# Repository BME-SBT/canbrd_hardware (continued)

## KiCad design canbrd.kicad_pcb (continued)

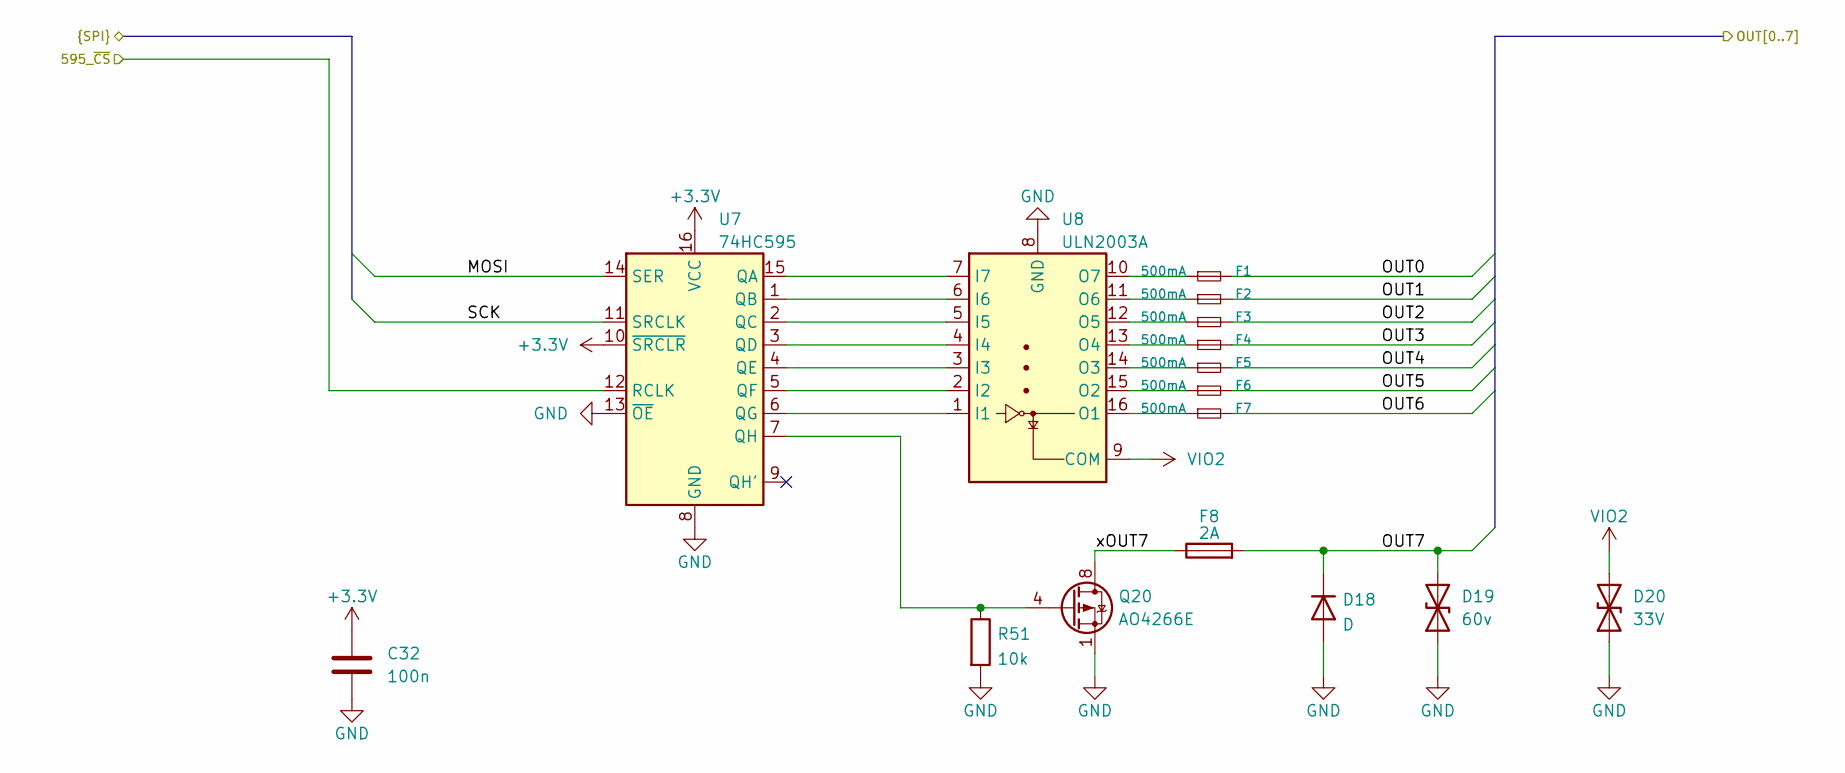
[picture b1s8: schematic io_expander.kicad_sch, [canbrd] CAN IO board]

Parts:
C32: 100n; C_0603_1608Metric
D18: D; D_SMB
D19: 60v; D_SMB
D20: 33V; D_SMB
F1, F2, F3, F4, F5, F6, F7: 500mA; Fuse_1206_3216Metric
F8: 2A; Littelfuse-154-2920
Q20: AO4266E; SOIC-8_3.9x4.9mm_P1.27mm
R51: 10k; R_0603_1608Metric
U7: 74HC595; SOIC-16_3.9x9.9mm_P1.27mm
U8: ULN2003A; SOIC-16_3.9x9.9mm_P1.27mm

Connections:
+3V3: C32.1, U7.10 (~SRCLR), U7.16 (VCC); also elsewhere on the board
/CAN/MOSI: U7.14 (SER); also elsewhere on the board
/CAN/SCK: U7.11 (SRCLK); also elsewhere on the board
/Connectors/OUT0: F1.2; also elsewhere on the board
/Connectors/OUT1: F2.2; also elsewhere on the board
/Connectors/OUT2: F3.2; also elsewhere on the board
/Connectors/OUT3: F4.2; also elsewhere on the board
/Connectors/OUT4: F5.2; also elsewhere on the board
/Connectors/OUT5: F6.2; also elsewhere on the board
/Connectors/OUT6: F7.2; also elsewhere on the board
/Connectors/OUT7: D18.1 (K), D19.2 (A2), F8.2; also elsewhere on the board
/IO Expander/595_~CS: U7.12 (RCLK); also elsewhere on the board
/IO Expander/xOUT7: F8.1, Q20.5 (D), Q20.6 (D), Q20.7 (D), Q20.8 (D)
GND: C32.2, D18.2 (A), D19.1 (A1), D20.1 (A1), Q20.1 (S), Q20.2 (S), Q20.3 (S), R51.2, U7.8 (GND), U7.13 (~OE), U8.8 (GND); also elsewhere on the board
unnamed: F1.1, U8.10 (O7)
unnamed: F2.1, U8.11 (O6)
unnamed: F3.1, U8.12 (O5)
unnamed: F4.1, U8.13 (O4)
unnamed: F5.1, U8.14 (O3)
unnamed: F6.1, U8.15 (O2)
unnamed: F7.1, U8.16 (O1)
unnamed: Q20.4 (G), R51.1, U7.7 (QH)
unnamed: U7.1 (QB), U8.6 (I6)
unnamed: U7.2 (QC), U8.5 (I5)
unnamed: U7.3 (QD), U8.4 (I4)
unnamed: U7.4 (QE), U8.3 (I3)
unnamed: U7.5 (QF), U8.2 (I2)
unnamed: U7.6 (QG), U8.1 (I1)
unnamed: U7.15 (QA), U8.7 (I7)
VIO2: D20.2 (A2), U8.9 (COM); also elsewhere on the board

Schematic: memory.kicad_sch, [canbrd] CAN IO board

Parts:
J2: Micro_SD_Card; GTFH081x1YHR
R52: 100; R_0603_1608Metric

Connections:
+3V3: J2.4 (VDD); also elsewhere on the board
/CAN/MISO: R52.1; also elsewhere on the board
/CAN/MOSI: J2.3 (CMD); also elsewhere on the board
/CAN/SCK: J2.5 (CLK); also elsewhere on the board
/MCU/SD_~CS: J2.2 (DAT3/CD); also elsewhere on the board
/SD/xMISO: J2.7 (DAT0), R52.2
GND: J2.6 (VSS), J2.9 (SHIELD); also elsewhere on the board

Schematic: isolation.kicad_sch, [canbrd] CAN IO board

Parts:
C25, C26: 10u; C_0805_2012Metric
C27: 1n; C_1206_3216Metric_Pad1.33x1.80mm_HandSolder; Voltage 2kV
PS1: RFM-0505S; CONV_RFM-0505S
R13, R15, R17: 680; R_0603_1608Metric
R14: 330; R_0603_1608Metric
R16: 5.1k; R_0603_1608Metric
R18: 10k; R_0603_1608Metric
U5, U6: 6N137S; SMDIP-8_W9.53mm

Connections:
+3V3: R14.1; also elsewhere on the board
+5V: C25.1, PS1.2 (+VIN), R15.1, U6.7 (EN), U6.8 (VCC); also elsewhere on the board
+5VISO: C26.1, PS1.4 (+VOUT), R13.1, R17.2, U5.7 (EN), U5.8 (VCC); also elsewhere on the board
/CAN/CAN_Rx: R16.1, R18.1; also elsewhere on the board
/CAN/CAN_Rx_ISO: U6.3 (C); also elsewhere on the board
/CAN/CAN_Tx: U5.3 (C); also elsewhere on the board
/CAN/CAN_Tx_ISO: R13.2, U5.6 (VO); also elsewhere on the board
GND: C25.2, C27.1, PS1.1 (-VIN), R18.2, U6.5 (GND); also elsewhere on the board
GNDISO: C26.2, C27.2, PS1.3 (-VOUT), U5.5 (GND); also elsewhere on the board
unnamed: R14.2, U5.2 (A)
unnamed: R15.2, R16.2, U6.6 (VO)
unnamed: R17.1, U6.2 (A)

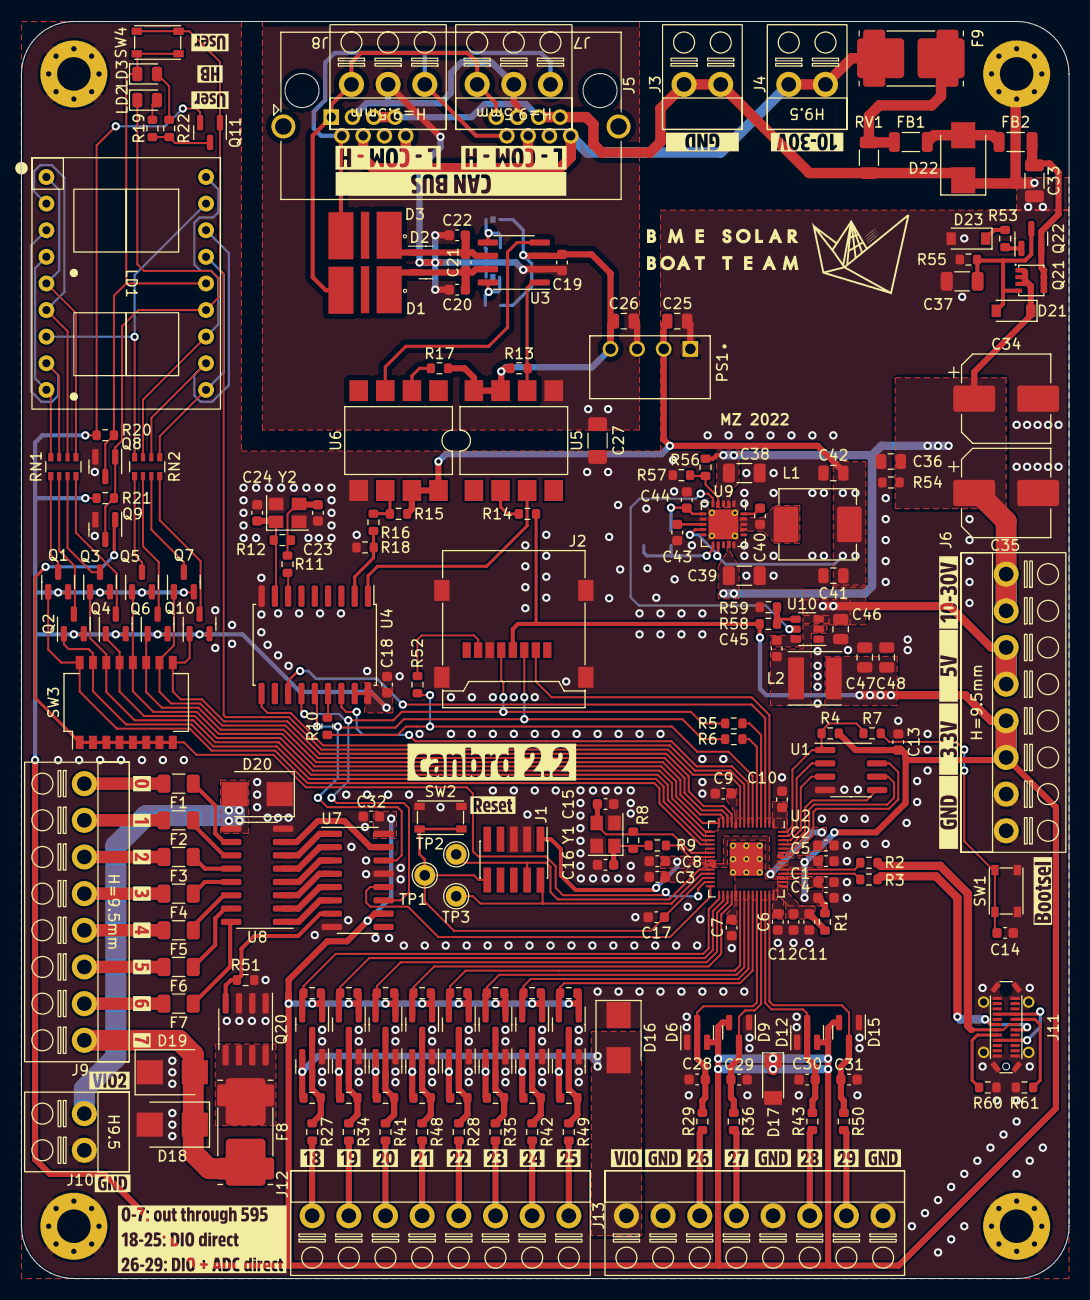
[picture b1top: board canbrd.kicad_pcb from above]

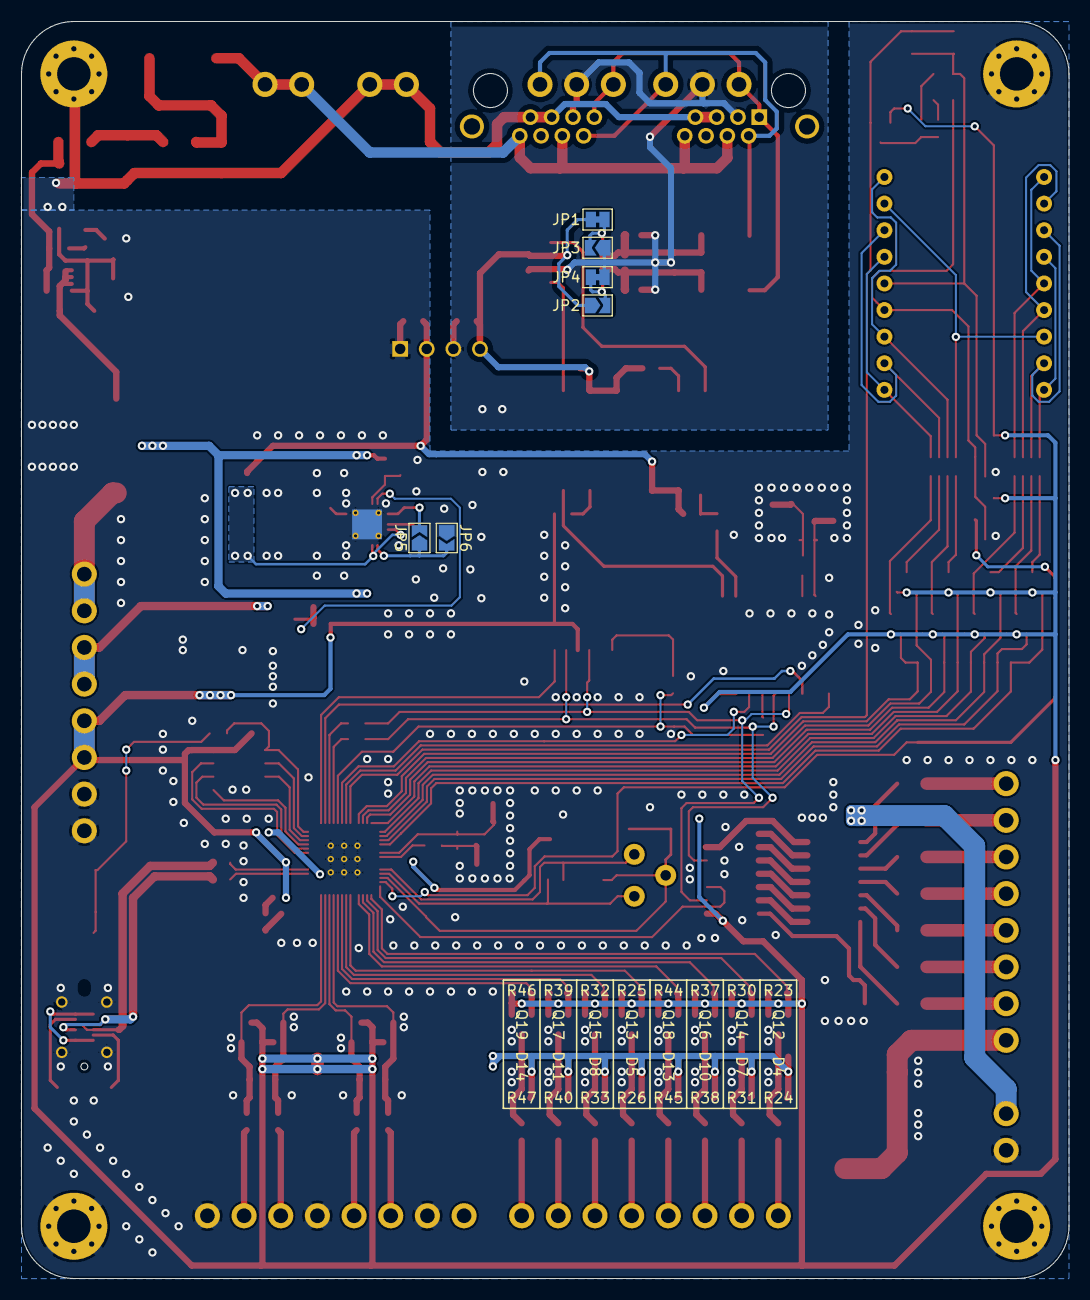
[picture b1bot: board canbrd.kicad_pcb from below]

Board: 2 copper layers, 100.0 x 120.0 mm, 258 parts (6 on the bottom side), 162 nets.

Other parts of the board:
kibuzzard-624B71BB: G***; kibuzzard-624B71BB
kibuzzard-624B71D2: G***; kibuzzard-624B71D2
kibuzzard-624B71E6: G***; kibuzzard-624B71E6
kibuzzard-624B71F2: G***; kibuzzard-624B71F2
kibuzzard-624B71FA: G***; kibuzzard-624B71FA
kibuzzard-624B75E6: G***; kibuzzard-624B75E6
kibuzzard-624B75EF: G***; kibuzzard-624B75EF
kibuzzard-624B75FB: G***; kibuzzard-624B75FB
kibuzzard-624B720A: G***; kibuzzard-624B720A
kibuzzard-624B724B: G***; kibuzzard-624B724B
kibuzzard-624B766D: G***; kibuzzard-624B766D
kibuzzard-624B7201: G***; kibuzzard-624B7201
kibuzzard-624B7210: G***; kibuzzard-624B7210
kibuzzard-624B7220: G***; kibuzzard-624B7220
kibuzzard-624B7229: G***; kibuzzard-624B7229
kibuzzard-624B7230: G***; kibuzzard-624B7230
kibuzzard-624B7237: G***; kibuzzard-624B7237
kibuzzard-624B7242: G***; kibuzzard-624B7242
kibuzzard-624B7247: G***; kibuzzard-624B7247
kibuzzard-624B7255: G***; kibuzzard-624B7255
kibuzzard-624B7539: G***; kibuzzard-624B7539
kibuzzard-624B7544: G***; kibuzzard-624B7544
kibuzzard-624B7558: G***; kibuzzard-624B7558
kibuzzard-624B7567: G***; kibuzzard-624B7567
kibuzzard-624B7585: G***; kibuzzard-624B7585
kibuzzard-62179C5E: G***; kibuzzard-62179C5E
kibuzzard-62179C9D: G***; kibuzzard-62179C9D
kibuzzard-62179CFC: G***; kibuzzard-62179CFC
kibuzzard-62179D4A: G***; kibuzzard-62179D4A
kibuzzard-62179F21: G***; kibuzzard-62179F21
kibuzzard-62991FA5, kibuzzard-62991FA5#2: G***; kibuzzard-62991FA5
kibuzzard-629153AB: G***; kibuzzard-629153AB
kibuzzard-629155A8: G***; kibuzzard-629155A8
kibuzzard-629155F9: G***; kibuzzard-629155F9
kibuzzard-629930A8: G***; kibuzzard-629930A8
kibuzzard-629930D0, kibuzzard-629930D0#2: G***; kibuzzard-629930D0
kibuzzard-62915456: G***; kibuzzard-62915456
kibuzzard-62915475: G***; kibuzzard-62915475
kibuzzard-62915589: G***; kibuzzard-62915589
kibuzzard-62992008: G***; kibuzzard-62992008

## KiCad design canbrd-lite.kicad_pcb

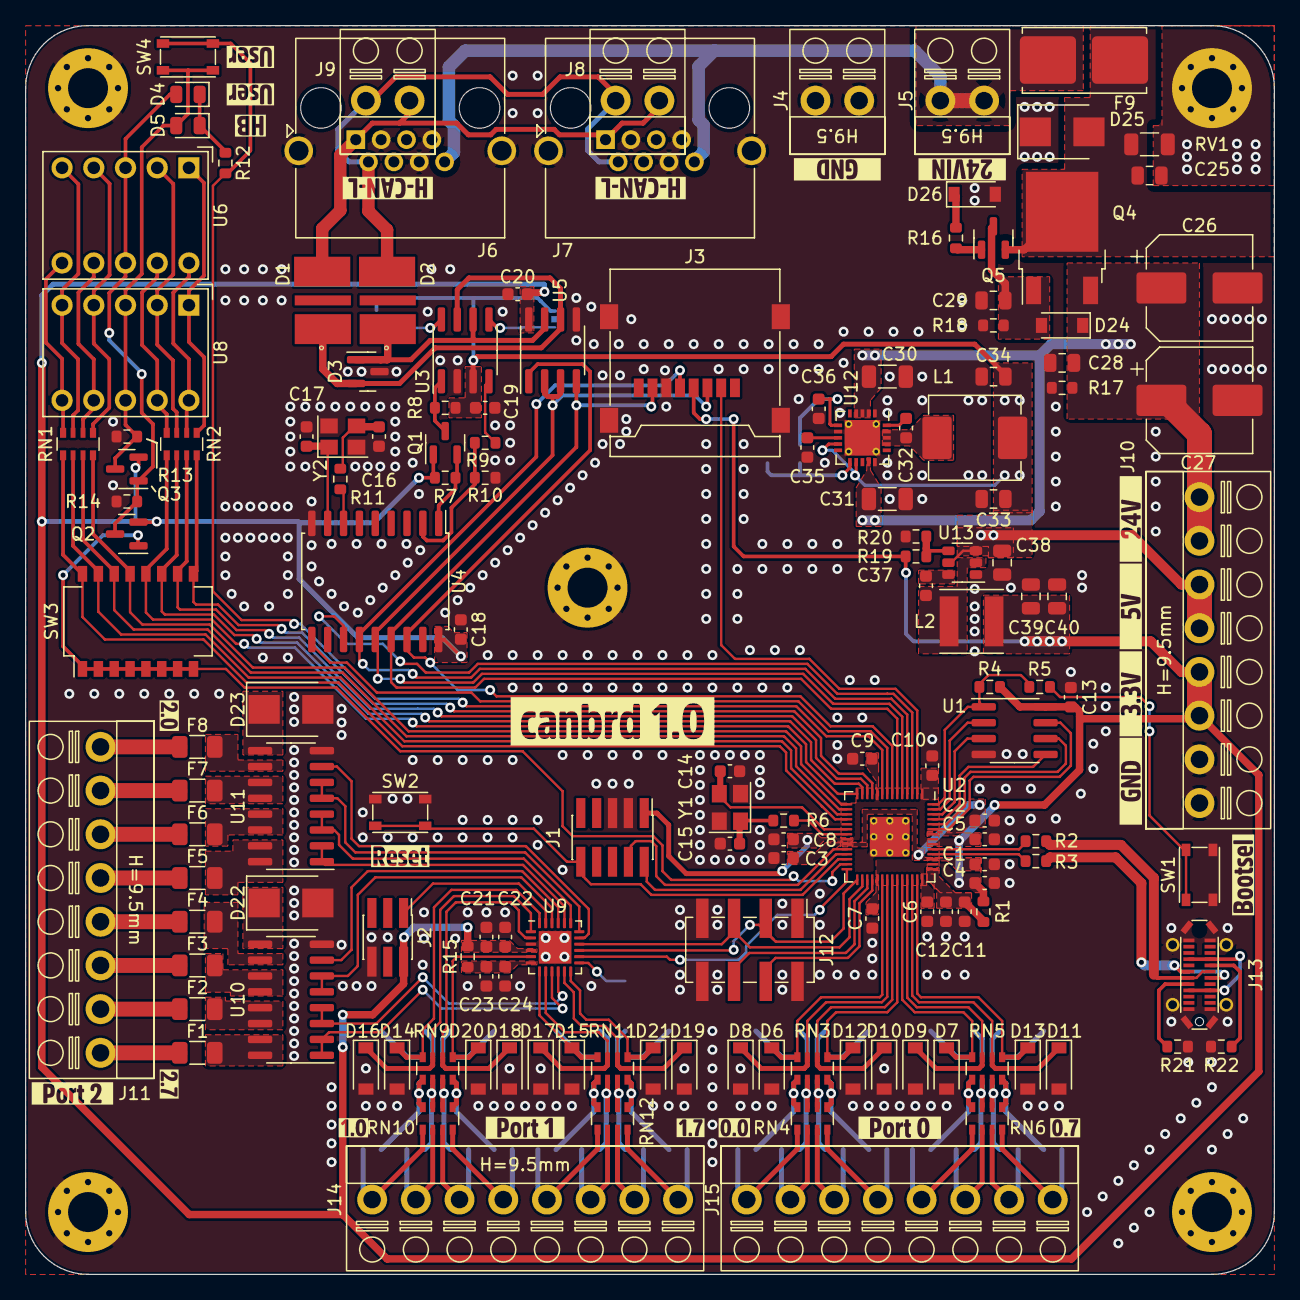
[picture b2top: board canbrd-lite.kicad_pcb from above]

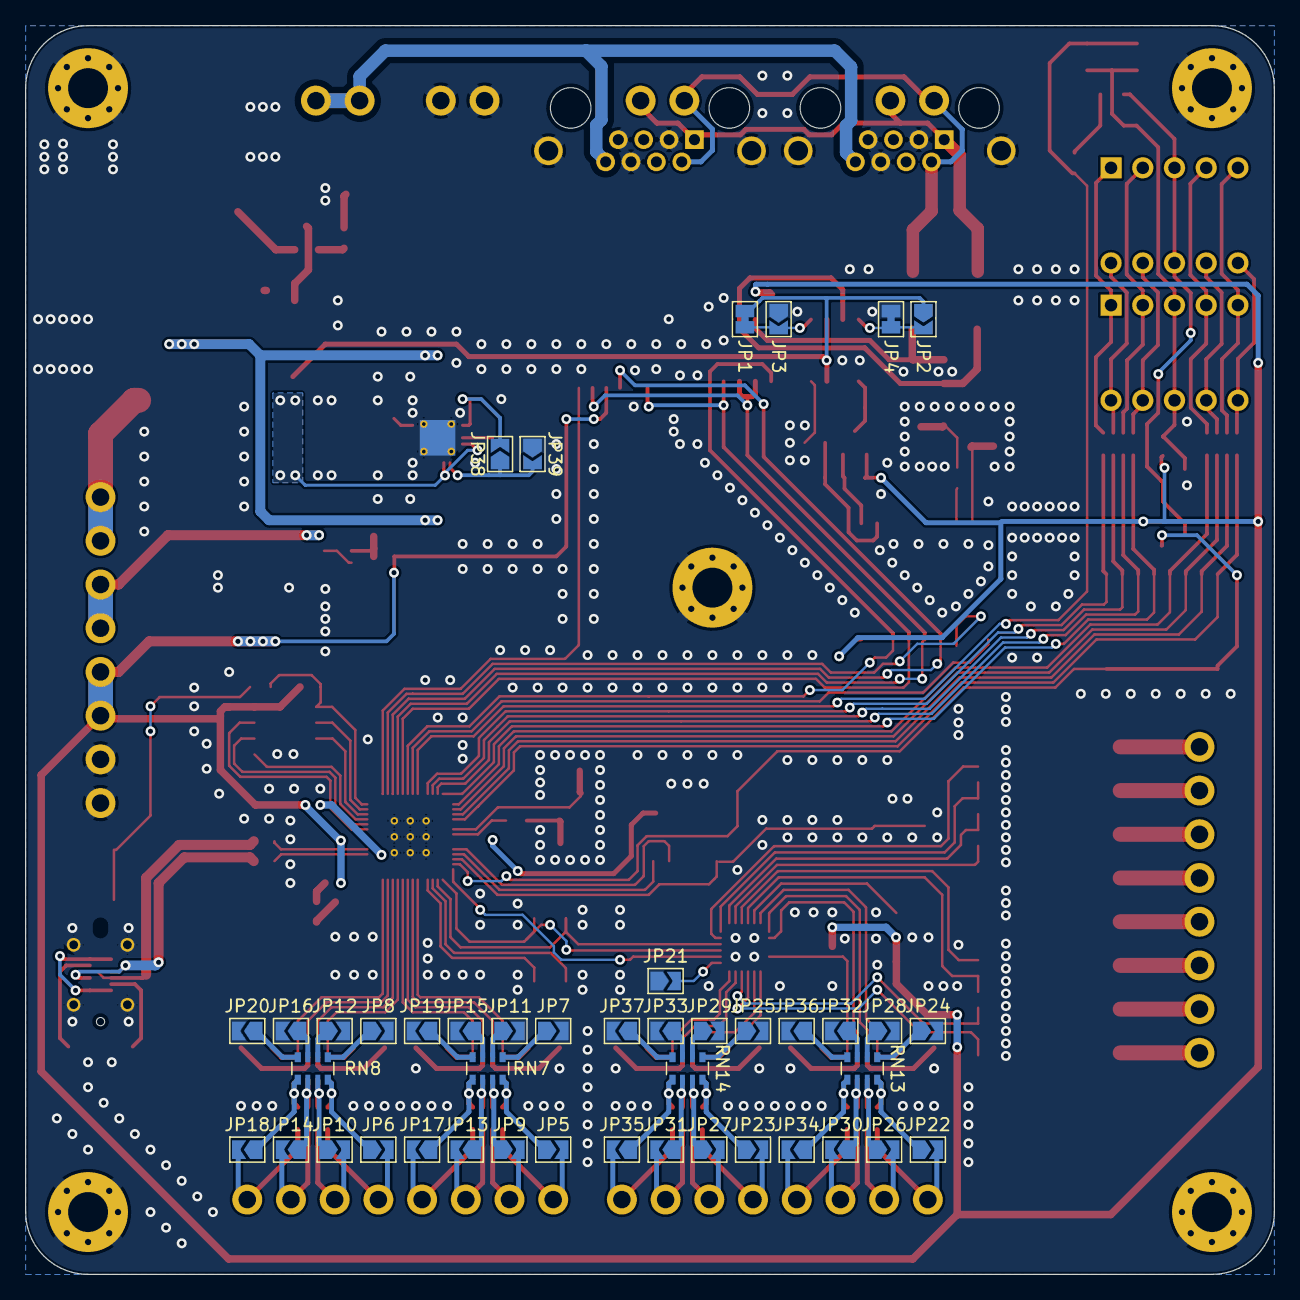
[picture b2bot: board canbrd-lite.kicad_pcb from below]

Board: 2 copper layers, 100.0 x 100.0 mm, 219 parts (43 on the bottom side), 178 nets.

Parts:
C1, C4, C11, C21, C23: 1u; C_0603_1608Metric
C2, C3, C5, C6, C7, C8, C9, C10, C12, C13, C18, C19, C20, C22, C24, C32, C37: 100n; C_0603_1608Metric
C14, C15, C16, C17: ???; C_0603_1608Metric
C25, C28, C29: 100n; C_0805_2012Metric
C26, C27: 47u; CP_Elec_8x6.5
C30, C31: 2.2u; C_1206_3216Metric
C33, C34, C39, C40: 22u; C_0805_2012Metric
C35: 5.6n; C_0603_1608Metric
C36: 2.2u; C_0603_1608Metric
C38: 10u; C_0805_2012Metric
D1, D2: TBU-CA; DIOC650X400X100N
D3: NUP2105L; SOT-23
D4: User; LED_0805_2012Metric
D5: Heartbeat; LED_0805_2012Metric
D6, D7, D8, D9, D10, D11, D12, D13, D14, D15, D16, D17, D18, D19, D20, D21: 3.3V; D_SOD-123
D22, D23, D25: 33V; D_SMB
D24: 10V; D_SOD-123
D26: 30V; D_SOD-123
F1, F2, F3, F5, F6, F7: 1A; Fuse_1206_3216Metric
F4, F8: 500mA; Fuse_1206_3216Metric
F9: 1A; Littelfuse-154
H1, H2, H3, H4, H5: M3; MountingHole_3.2mm_M3_Pad_Via
J1: RP_DEBUG; PinHeader_2x05_P1.27mm_Vertical_SMD
J2: UPDI; PinHeader_2x03_P1.27mm_Vertical_SMD
J3: Micro_SD_Card; GTFH081x1YHR
J4: GND; NH0210x0xxxxG
J5: Field24V; NH0210x0xxxxG
J6, J7: Amphenol RJHSE5380; RJ45_Amphenol_RJHSE5380
J8, J9: CAN; NH0210x0xxxxG
J10: PwrOut; NH0810x0xxxxG
J11: IO2; NH0810x0xxxxG
J12: I^{2}C; PinHeader_2x04_P2.54mm_Vertical_SMD
J13: USB_C_Receptacle; 10132328
J14: IO1; NH0810x0xxxxG
J15: IO0; NH0810x0xxxxG
JP1: Pin5H; SolderJumper-2_P1.3mm_Bridged_Pad1.0x1.5mm
JP2: Pin8H; SolderJumper-2_P1.3mm_Open_TrianglePad1.0x1.5mm
JP3: Pin5L; SolderJumper-2_P1.3mm_Open_TrianglePad1.0x1.5mm
JP4: Pin8L; SolderJumper-2_P1.3mm_Bridged_Pad1.0x1.5mm
JP5, JP6, JP9, JP10, JP13, JP14, JP17, JP18, JP22, JP23, JP26, JP27, JP30, JP31, JP34, JP35: LowZ; SolderJumper-2_P1.3mm_Open_TrianglePad1.0x1.5mm
JP7, JP8, JP11, JP12, JP15, JP16, JP19, JP20, JP24, JP25, JP28, JP29, JP32, JP33, JP36, JP37: Vdiv; SolderJumper-2_P1.3mm_Open_TrianglePad1.0x1.5mm
JP21: Addr; SolderJumper-2_P1.3mm_Open_TrianglePad1.0x1.5mm
JP38: DCM; SolderJumper-2_P1.3mm_Open_TrianglePad1.0x1.5mm
JP39: PWM; SolderJumper-2_P1.3mm_Open_TrianglePad1.0x1.5mm
L1: 6.8u; L_Abracon_ASPI-0630LR
L2: 2.2u; L_Taiyo-Yuden_NR-50xx
Q1: 2N7002K; SOT-23
Q2, Q3: BSS83P; SOT-23
Q4: Q_PMOS_GDS; TO-252-2
Q5: BC856; SOT-23
R1, R15: 220; R_0603_1608Metric
R2, R3: 27; R_0603_1608Metric
R4, R10, R17, R18, R20: 10k; R_0603_1608Metric
R5, R6, R7, R8, R11, R13, R14, R16: 1k; R_0603_1608Metric
R9: 4k7; R_0603_1608Metric
R12: 470; R_0603_1608Metric
R19: 31.6k; R_0603_1608Metric
R21, R22: 5.1k; R_0603_1608Metric
RN1, RN2: 470; R_Array_Convex_4x0603
RN3, RN5: 330; R_Array_Convex_4x0603
RN4, RN6, RN10, RN12: 10k; R_Array_Convex_4x0603
RN7, RN8, RN13, RN14: 1k; R_Array_Convex_4x0603
RN9, RN11: 68; R_Array_Convex_4x0603
RV1: 30V; R_1206_3216Metric
SW1: BOOTSEL; PTS815-SJ
SW2: RESET; PTS815-SJ
SW3: SW_DIP_x08; SW_DIP_SPSTx08_Slide_KingTek_DSHP08TS_W7.62mm_P1.27mm
SW4: User; PTS815-SJ
U1: W25Q16JVSNIQ; SOIC-8_3.9x4.9mm_P1.27mm
U2: RP2040; RP2040-QFN-56
U3: TJA1051T-3; SOIC-8_3.9x4.9mm_P1.27mm
U4: MCP2510-x/SO; SOIC-18W_7.5x11.6mm_P1.27mm
U5: MAX3485CSA; SOIC-8_3.9x4.9mm_P1.27mm
U6, U8: 157119S12801; Sx39-1xxxxx
U9: ATtiny427; QFN-24-1EP_4x4mm_P0.5mm_EP2.6x2.6mm
U10, U11: ULN2003A; SOIC-16_3.9x9.9mm_P1.27mm
U12: MAX17634BATP+; TQFN20-EP
U13: AP62250WU; TSOT26
Y1: 12MHz; Crystal_SMD_3225-4Pin_3.2x2.5mm
Y2: 16MHz; Crystal_SMD_3225-4Pin_3.2x2.5mm
kibuzzard-621B6EAC: G***; kibuzzard-621B6EAC
kibuzzard-621B6EB9: G***; kibuzzard-621B6EB9
kibuzzard-621B6EDA: G***; kibuzzard-621B6EDA
kibuzzard-6217A0B8: G***; kibuzzard-6217A0B8
kibuzzard-6217A0C8: G***; kibuzzard-6217A0C8
kibuzzard-6217A0EA: G***; kibuzzard-6217A0EA
kibuzzard-6217A003: G***; kibuzzard-6217A003
kibuzzard-6217A03E: G***; kibuzzard-6217A03E
kibuzzard-6217A08D: G***; kibuzzard-6217A08D
kibuzzard-6217A022: G***; kibuzzard-6217A022
kibuzzard-62179C2A: G***; kibuzzard-62179C2A
kibuzzard-62179C5E: G***; kibuzzard-62179C5E
kibuzzard-62179C9D: G***; kibuzzard-62179C9D
kibuzzard-62179CFC: G***; kibuzzard-62179CFC
kibuzzard-62179D4A: G***; kibuzzard-62179D4A
kibuzzard-62179E31: G***; kibuzzard-62179E31
kibuzzard-62179E98: G***; kibuzzard-62179E98
kibuzzard-62179EAF: G***; kibuzzard-62179EAF
kibuzzard-62179F8F: G***; kibuzzard-62179F8F
kibuzzard-62179F9F: G***; kibuzzard-62179F9F
kibuzzard-62179F21: G***; kibuzzard-62179F21
kibuzzard-62179FB2: G***; kibuzzard-62179FB2
kibuzzard-621788DF: G***; kibuzzard-621788DF

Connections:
+1V1: C1.1, C2.1, C3.1, U2.23 (DVDD), U2.45 (VREG_VOUT), U2.50 (DVDD)
+3.3VA: C11.1, C12.1, R1.2, U2.43 (ADC_AVDD)
+3.3VA2: C23.1, C24.1, R15.2, U9.6 (PA5)
+3V3: C4.1, C5.1, C6.1, C7.1, C8.1, C9.1, C10.1, C13.1, C18.1, C20.1, C21.1, C22.1, C39.1, C40.1, J1.1 (VTref), J2.2, J3.4 (VDD), J10.3, J10.4, L2.2, Q1.1 (G), Q2.2 (S), Q3.2 (S), R1.1, R4.1, R7.1, R15.1, R19.1, U1.8 (VCC), U2.1 (IOVDD), U2.10 (IOVDD), U2.22 (IOVDD), U2.33 (IOVDD), U2.42 (IOVDD), U2.44 (VREG_IN), U2.48 (USB_VDD), U2.49 (IOVDD), U4.18 (VDD), U5.8 (VCC), U9.4 (VCC)
+5V: C19.1, C33.1, C34.1, C38.1, J10.5, J10.6, JP1.2 (B), JP2.1 (A), L1.2, R8.1, U3.3 (VCC), U12.9 (FB), U12.12 (EXTVCC), U13.3 (VIN), U13.5 (EN)
+24V: C26.1, C27.1, C28.1, C30.1, C31.1, D24.1 (K), J10.7, J10.8, Q4.3 (S), R17.1, U12.2 (IN), U12.3 (IN), U12.4 (EN/UVLO), U12.14 (IN)
/CAN/CANH: D1.3, J6.1, J7.1, J8.1, J9.1
/CAN/CANL: D2.3, J6.2, J7.2, J8.2, J9.2
/CAN/CAN_OSC1: C17.2, U4.8 (OSC1), Y2.1
/CAN/CAN_OSC2: C16.2, R11.1, Y2.3
/CAN/CAN_Rx_HV: R9.2, U3.4 (RXD)
/CAN/CAN_Rx_LV: R9.1, R10.1, U4.2 (RXCAN)
/CAN/CAN_Tx_HV: Q1.3 (D), R8.2, U3.1 (TXD)
/CAN/CAN_Tx_LV: Q1.2 (S), R7.2, U4.1 (TXCAN)
/CAN/MISO: J3.7 (DAT0), U2.6 (GPIO4), U4.15 (SO), U5.4 (DI)
/CAN/MOSI: J3.3 (CMD), U2.5 (GPIO3), U4.14 (SI), U5.2 (~RE), U5.3 (DE)
/CAN/Pin5: JP1.1 (A), JP3.2 (B), U3.5 (VIO)
/CAN/Pin8: JP2.2 (B), JP4.1 (A), U3.8 (S)
/CAN/SCK: J3.5 (CLK), U2.4 (GPIO2), U4.13 (SCK)
/CAN/~CS: U2.7 (GPIO5), U4.16 (~CS), U5.1 (RO)
/CAN/~INT: U2.3 (GPIO1), U4.12 (~INT)
/CAN/~RX1: U2.8 (GPIO6), U4.10 (~RX1BF)
/Connectors/EXT.0: J12.6, U2.31 (GPIO20)
/Connectors/EXT.1: J12.4, U2.32 (GPIO21)
/Connectors/Field24V: F9.1, J5.1, J5.2, J6.8, J7.8
/Connectors/IO0.0: J15.1, JP5.2 (B), RN4.1 (R1.1)
/Connectors/IO0.1: J15.2, JP9.2 (B), RN4.2 (R2.1)
/Connectors/IO0.2: J15.3, JP13.2 (B), RN4.3 (R3.1)
/Connectors/IO0.3: J15.4, JP17.2 (B), RN4.4 (R4.1)
/Connectors/IO0.4: J15.5, JP6.2 (B), RN6.1 (R1.1)
/Connectors/IO0.5: J15.6, JP10.2 (B), RN6.2 (R2.1)
/Connectors/IO0.6: J15.7, JP14.2 (B), RN6.3 (R3.1)
/Connectors/IO0.7: J15.8, JP18.2 (B), RN6.4 (R4.1)
/Connectors/IO1.0: J14.1, JP22.2 (B), RN10.1 (R1.1)
/Connectors/IO1.1: J14.2, JP26.2 (B), RN10.2 (R2.1)
/Connectors/IO1.2: J14.3, JP30.2 (B), RN10.3 (R3.1)
/Connectors/IO1.3: J14.4, JP34.2 (B), RN10.4 (R4.1)
/Connectors/IO1.4: J14.5, JP23.2 (B), RN12.1 (R1.1)
/Connectors/IO1.5: J14.6, JP27.2 (B), RN12.2 (R2.1)
/Connectors/IO1.6: J14.7, JP31.2 (B), RN12.3 (R3.1)
/Connectors/IO1.7: J14.8, JP35.2 (B), RN12.4 (R4.1)
/Connectors/IO2.0: F8.2, J11.1
/Connectors/IO2.1: F7.2, J11.2
/Connectors/IO2.2: F6.2, J11.3
/Connectors/IO2.3: F5.2, J11.4
/Connectors/IO2.4: F4.2, J11.5
/Connectors/IO2.5: F3.2, J11.6
/Connectors/IO2.6: F2.2, J11.7
/Connectors/IO2.7: F1.2, J11.8
/Connectors/SCL: J12.5, U2.30 (GPIO19), U9.16 (PB0)
/Connectors/SDA: J12.3, U2.29 (GPIO18), U9.15 (PB1)
/Connectors/USB+: J13.A6 (D+), J13.B6 (D+), R2.2
/Connectors/USB-: J13.A7 (D-), J13.B7 (D-), R3.2
/DISP+SW/Dig: Q2.1 (G), SW3.1, SW3.2, SW3.3, SW3.4, SW3.5, SW3.6, SW3.7, SW3.8, U2.27 (GPIO16)
/DISP+SW/Seg.0: RN1.1 (R1.1), SW3.16, U2.18 (GPIO15)
/DISP+SW/Seg.1: RN1.2 (R2.1), SW3.15, U2.17 (GPIO14)
/DISP+SW/Seg.2: RN1.3 (R3.1), SW3.14, U2.16 (GPIO13)
/DISP+SW/Seg.3: RN1.4 (R4.1), SW3.13, U2.15 (GPIO12)
/DISP+SW/Seg.4: RN2.1 (R1.1), SW3.12, U2.14 (GPIO11)
/DISP+SW/Seg.5: RN2.2 (R2.1), SW3.11, U2.13 (GPIO10)
/DISP+SW/Seg.6: RN2.3 (R3.1), SW3.10, U2.12 (GPIO9)
/DISP+SW/Seg.7: RN2.4 (R4.1), SW3.9, U2.11 (GPIO8)
/DISP+SW/Seg.8: R12.2, SW4.2, U2.9 (GPIO7)
/DISP+SW/SegR.0: RN1.8 (R1.2), U6.6 (DP), U8.6 (DP)
/DISP+SW/SegR.1: RN1.7 (R2.2), U6.5 (D), U8.5 (D)
/DISP+SW/SegR.2: RN1.6 (R3.2), U6.7 (C), U8.7 (C)
/DISP+SW/SegR.3: RN1.5 (R4.2), U6.4 (E), U8.4 (E)
/DISP+SW/SegR.4: RN2.8 (R1.2), U6.9 (B), U8.9 (B)
/DISP+SW/SegR.5: RN2.7 (R2.2), U6.2 (F), U8.2 (F)
/DISP+SW/SegR.6: RN2.6 (R3.2), U6.10 (A), U8.10 (A)
/DISP+SW/SegR.7: RN2.5 (R4.2), U6.1 (G), U8.1 (G)
/DISP+SW/SegR.8: D4.1 (K), D5.1 (K), R12.1
/DISP+SW/nDig: D4.2 (A), Q2.3 (D), Q3.1 (G), R14.1, U6.3 (CA), U6.8 (CA)
/DISP+SW/~nDig: D5.2 (A), Q3.3 (D), R13.1, SW4.1, U8.3 (CA), U8.8 (CA)
/IO Expander/AT_ADDR: JP21.2 (B), U9.13 (PB3)
/IO Expander/AT_~INT: U2.28 (GPIO17), U9.14 (PB2)
/IO Expander/IO Expander Power IO/AT2.0: U9.17 (PC0), U11.7 (I7)
/IO Expander/IO Expander Power IO/AT2.1: U9.18 (PC1), U11.5 (I5), U11.6 (I6)
/IO Expander/IO Expander Power IO/AT2.2: U9.19 (PC2), U11.3 (I3), U11.4 (I4)
/IO Expander/IO Expander Power IO/AT2.3: U9.20 (PC3), U11.1 (I1), U11.2 (I2)
/IO Expander/IO Expander Power IO/AT2.4: U9.21 (PC4), U10.7 (I7)
/IO Expander/IO Expander Power IO/AT2.5: U9.22 (PC5), U10.5 (I5), U10.6 (I6)
/IO Expander/IO Expander Power IO/AT2.6: U9.10 (PB6), U10.3 (I3), U10.4 (I4)
/IO Expander/IO Expander Power IO/AT2.7: U9.9 (PB7), U10.1 (I1), U10.2 (I2)
/IO Expander/IO Expander Power IO/COM0: D22.1 (A1), U10.9 (COM)
/IO Expander/IO Expander Power IO/COM1: D23.1 (A1), U11.9 (COM)
/IO Expander/IO Expander Power IO/HC0: F1.1, U10.15 (O2), U10.16 (O1)
/IO Expander/IO Expander Power IO/HC1: F2.1, U10.13 (O4), U10.14 (O3)
/IO Expander/IO Expander Power IO/HC2: F3.1, U10.11 (O6), U10.12 (O5)
/IO Expander/IO Expander Power IO/HC3: F4.1, U10.10 (O7)
/IO Expander/IO Expander Power IO/HC4: F5.1, U11.15 (O2), U11.16 (O1)
/IO Expander/IO Expander Power IO/HC5: F6.1, U11.13 (O4), U11.14 (O3)
/IO Expander/IO Expander Power IO/HC6: F7.1, U11.11 (O6), U11.12 (O5)
/IO Expander/IO Expander Power IO/HC7: F8.1, U11.10 (O7)
/IO Expander/IO Expander Protection/AT1.0: D14.1 (K), RN9.8 (R1.2), U9.24 (PA1)
/IO Expander/IO Expander Protection/AT1.1: D16.1 (K), RN9.7 (R2.2), U9.1 (PA2)
/IO Expander/IO Expander Protection/AT1.2: D18.1 (K), RN9.6 (R3.2), U9.2 (PA3)
/IO Expander/IO Expander Protection/AT1.3: D20.1 (K), RN9.5 (R4.2), U9.5 (PA4)
/IO Expander/IO Expander Protection/AT1.4: D15.1 (K), RN11.8 (R1.2), U9.7 (PA6)
/IO Expander/IO Expander Protection/AT1.5: D17.1 (K), RN11.7 (R2.2), U9.8 (PA7)
/IO Expander/IO Expander Protection/AT1.6: D19.1 (K), RN11.6 (R3.2), U9.11 (PB5)
/IO Expander/IO Expander Protection/AT1.7: D21.1 (K), RN11.5 (R4.2), U9.12 (PB4)
/IO Expander/UPDI: J2.1, U9.23 (~RESET/PA0)
/IO/RP0: D6.1 (K), RN3.8 (R1.2), U2.34 (GPIO22)
/IO/RP1: D8.1 (K), RN3.7 (R2.2), U2.35 (GPIO23)
/IO/RP2: D10.1 (K), RN3.6 (R3.2), U2.36 (GPIO24)
/IO/RP3: D12.1 (K), RN3.5 (R4.2), U2.37 (GPIO25)
/IO/RP4: D7.1 (K), RN5.8 (R1.2), U2.38 (GPIO26_ADC0)
/IO/RP5: D9.1 (K), RN5.7 (R2.2), U2.39 (GPIO27_ADC1)
/IO/RP6: D11.1 (K), RN5.6 (R3.2), U2.40 (GPIO28_ADC2)
/IO/RP7: D13.1 (K), RN5.5 (R4.2), U2.41 (GPIO29_ADC3)
/MCU/QSPI_CLK: U1.6 (CLK), U2.52 (QSPI_SCLK)
/MCU/QSPI_IO0: U1.5 (DI/IO0), U2.53 (QSPI_SD0)
/MCU/QSPI_IO1: U1.2 (DO/IO1), U2.55 (QSPI_SD1)
/MCU/QSPI_IO2: U1.3 (~WP/IO2), U2.54 (QSPI_SD2)
/MCU/QSPI_IO3: U1.7 (~HOLD/IO3), U2.51 (QSPI_SD3)
/MCU/QSPI_~CS: R4.2, R5.1, U1.1 (~CS), U2.56 (QSPI_SS)
/MCU/RP_SWCLK: J1.4 (SWDCLK/TCK), U2.24 (SWCLK)
/MCU/RP_SWDIO: J1.2 (SWDIO/TMS), U2.25 (SWD)
/MCU/RP_XIN: C14.2, U2.20 (XIN), Y1.3
/MCU/RP_XOUT: C15.2, R6.1, Y1.1
/MCU/RP_~RESET: J1.10 (~RESET), SW2.2, U2.26 (RUN)
/MCU/SD_~CS: J3.2 (DAT3/CD), U2.2 (GPIO0)
/MCU/USB_XDM: R3.1, U2.46 (USB_DM)
/MCU/USB_XDP: R2.1, U2.47 (USB_DP)
/MCU/~BOOTSEL: R5.2, SW1.1
/Power/AP_BST: C37.1, U13.6 (BST)
/Power/AP_FB: R19.2, R20.1, U13.4 (FB)
/Power/Fused24V: C25.1, D25.2 (A2), F9.2, Q4.2 (D), Q5.2 (E), RV1.1
/Power/MAX_BST: C32.1, U12.20 (BST)
/Power/MAX_INTVCC: C36.1, JP38.2 (B), U12.6 (INTVCC)
/Power/MAX_LX: C32.2, L1.1, U12.17 (LX), U12.18 (LX), U12.19 (LX)
/Power/MAX_MODE: JP38.1 (A), JP39.2 (B), U12.11 (MODE/SYNC)
/Power/MAX_SS: C35.1, U12.8 (SS)
/Power/SW3v3: C37.2, L2.1, U13.2 (SW)
/Power/revprot_gate: C29.1, D24.2 (A), Q4.1 (G), Q5.3 (C), R18.1
GND: C1.2, C2.2, C3.2, C4.2, C5.2, C6.2, C7.2, C8.2, C9.2, C10.2, C11.2, C12.2, C13.2, C14.1, C15.1, C16.1, C17.1, C18.2, C19.2, C20.2, C21.2, C22.2, C23.2, C24.2, C25.2, C26.2, C27.2, C28.2, C29.2, C30.2, C31.2, C33.2, C34.2, C35.2, C36.2, C38.2, C39.2, C40.2, D3.3 (A), D6.2 (A), D7.2 (A), D8.2 (A), D9.2 (A), D10.2 (A), D11.2 (A), D12.2 (A), D13.2 (A), D14.2 (A), D15.2 (A), D16.2 (A), D17.2 (A), D18.2 (A), D19.2 (A), D20.2 (A), D21.2 (A), D22.2 (A2), D23.2 (A2), D25.1 (A1), D26.2 (A), H1.1, H2.1, H3.1, H4.1, H5.1, J1.3 (GND), J1.5 (GND), J2.6, J3.6 (VSS), J3.9 (SHIELD), J4.1, J4.2, J6.3, J6.6, J6.7, J6.SH, J7.3, J7.6, J7.7, J7.SH, J10.1, J10.2, J12.1, J12.2, J12.7, J12.8, J13.A1 (GND), J13.A12 (GND), J13.B1 (GND), J13.B12 (GND), J13.S1 (SHIELD), JP3.1 (A), JP4.2 (B), JP7.2 (B), JP8.2 (B), JP11.2 (B), JP12.2 (B), JP15.2 (B), JP16.2 (B), JP19.2 (B), JP20.2 (B), JP21.1 (A), JP24.2 (B), JP25.2 (B), JP28.2 (B), JP29.2 (B), JP32.2 (B), JP33.2 (B), JP36.2 (B), JP37.2 (B), JP39.1 (A), R10.2, R13.2, R14.2, R17.2, R18.2, R20.2, R21.2, R22.2, RV1.2, SW1.2, SW2.1, U1.4 (GND), U2.19 (TESTEN), U2.57 (GND), U3.2 (GND), U4.9 (VSS), U5.5 (GND), U9.3 (GND), U9.25 (GND), U10.8 (GND), U11.8 (GND), U12.1 (PGND), U12.7 (SGND), U12.15 (PGND), U12.21 (EXP), U13.1 (GND), Y1.2, Y1.4, Y2.2, Y2.4
unnamed: D1.1, D3.2 (K), U3.7 (CANH), U5.6 (A)
unnamed: D2.1, D3.1 (K), U3.6 (CANL), U5.7 (B)
unnamed: D26.1 (K), R16.1
unnamed: J13.A5 (CC1), R21.1
unnamed: J13.B5 (CC2), R22.1
unnamed: JP5.1 (A), RN3.1 (R1.1), RN4.8 (R1.2), RN7.8 (R1.2)
unnamed: JP6.1 (A), RN5.1 (R1.1), RN6.8 (R1.2), RN8.8 (R1.2)
unnamed: JP7.1 (A), RN7.1 (R1.1)
unnamed: JP8.1 (A), RN8.1 (R1.1)
unnamed: JP9.1 (A), RN3.2 (R2.1), RN4.7 (R2.2), RN7.7 (R2.2)
unnamed: JP10.1 (A), RN5.2 (R2.1), RN6.7 (R2.2), RN8.7 (R2.2)
unnamed: JP11.1 (A), RN7.2 (R2.1)
unnamed: JP12.1 (A), RN8.2 (R2.1)
unnamed: JP13.1 (A), RN3.3 (R3.1), RN4.6 (R3.2), RN7.6 (R3.2)
unnamed: JP14.1 (A), RN5.3 (R3.1), RN6.6 (R3.2), RN8.6 (R3.2)
unnamed: JP15.1 (A), RN7.3 (R3.1)
unnamed: JP16.1 (A), RN8.3 (R3.1)
unnamed: JP17.1 (A), RN3.4 (R4.1), RN4.5 (R4.2), RN7.5 (R4.2)
unnamed: JP18.1 (A), RN5.4 (R4.1), RN6.5 (R4.2), RN8.5 (R4.2)
unnamed: JP19.1 (A), RN7.4 (R4.1)
unnamed: JP20.1 (A), RN8.4 (R4.1)
unnamed: JP22.1 (A), RN9.1 (R1.1), RN10.8 (R1.2), RN13.8 (R1.2)
unnamed: JP23.1 (A), RN11.1 (R1.1), RN12.8 (R1.2), RN14.8 (R1.2)
unnamed: JP24.1 (A), RN13.1 (R1.1)
unnamed: JP25.1 (A), RN14.1 (R1.1)
unnamed: JP26.1 (A), RN9.2 (R2.1), RN10.7 (R2.2), RN13.7 (R2.2)
unnamed: JP27.1 (A), RN11.2 (R2.1), RN12.7 (R2.2), RN14.7 (R2.2)
unnamed: JP28.1 (A), RN13.2 (R2.1)
unnamed: JP29.1 (A), RN14.2 (R2.1)
unnamed: JP30.1 (A), RN9.3 (R3.1), RN10.6 (R3.2), RN13.6 (R3.2)
unnamed: JP31.1 (A), RN11.3 (R3.1), RN12.6 (R3.2), RN14.6 (R3.2)
unnamed: JP32.1 (A), RN13.3 (R3.1)
unnamed: JP33.1 (A), RN14.3 (R3.1)
unnamed: JP34.1 (A), RN9.4 (R4.1), RN10.5 (R4.2), RN13.5 (R4.2)
unnamed: JP35.1 (A), RN11.4 (R4.1), RN12.5 (R4.2), RN14.5 (R4.2)
unnamed: JP36.1 (A), RN13.4 (R4.1)
unnamed: JP37.1 (A), RN14.4 (R4.1)
unnamed: Q5.1 (B), R16.2
unnamed: R6.2, U2.21 (XOUT)
unnamed: R11.2, U4.7 (OSC2)
VBUS: J13.A4 (VBUS), J13.A9 (VBUS), J13.B4 (VBUS), J13.B9 (VBUS)

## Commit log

2022-01-22 Init
2022-01-28 started routing
2022-02-24 Done?
2022-02-24 Add version, date
2022-02-27 WIP: display
2022-02-28 Done. I hope.
2022-03-07 Should be final
2022-03-14 rename project to canbrd
2022-03-14 rename project
2022-03-14 remove backups from git
2022-03-18 rev1.1: Add I2C pullups
2022-03-28 pre-simplification
2022-04-10 lots changed
2022-04-11 things changed
2022-04-11 Update gerber
2022-06-03 isolate and other stuff
2022-06-03 remove step from git
2023-02-06 Minimal design for testing
